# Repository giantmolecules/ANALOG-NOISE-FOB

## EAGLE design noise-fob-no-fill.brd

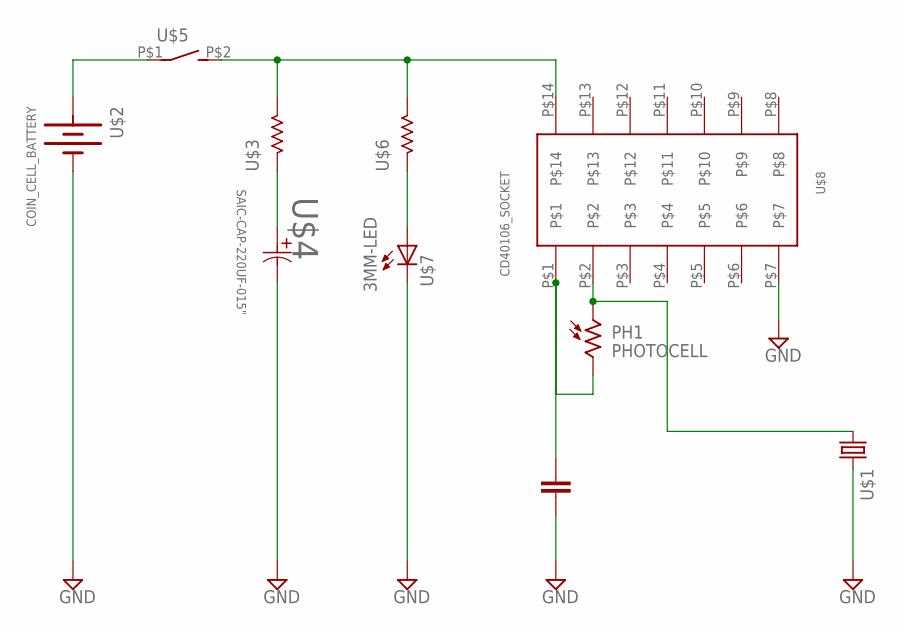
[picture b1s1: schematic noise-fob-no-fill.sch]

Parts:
PH1: PHOTOCELL
U$1: PIEZO_BUZZER_2
U$2: COIN_CELL_BATTERY; COIN_BATTERY
U$3, U$6: RESISTOR-1/4W-THROUGH-HOLE; 1/4W_TH_RESISTOR
U$4: SAIC-CAP-220UF-015"; SAIC-CAP-0.15"-LEAD-SPACING-01
U$5: TACTILE_SWITCH
U$7: 3MM-LED; LED3MM
U$8: CD40106_SOCKET; DIP_14_SOCKET
U$10: SAIC-CAP-0.1UF-02"; SAIC-CAP-0.2"-LEAD-SPACING-03

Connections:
GND: U$1.P$2 (2), U$2.P$2 (-), U$4.P$2 (22), U$7.K (2), U$8.P$7, U$10.P$1 (1)
unnamed: U$2.P$1 (+), U$5.P$1
unnamed: U$3.P$2, U$5.P$2 (S), U$6.P$2, U$8.P$14
unnamed: U$3.P$1, U$4.P$1 (11)
unnamed: U$6.P$1, U$7.A (1)
unnamed: PH1.P$1 (1), U$1.P$1 (1), U$8.P$2
unnamed: PH1.P$2 (2), U$8.P$1, U$10.P$2 (2)

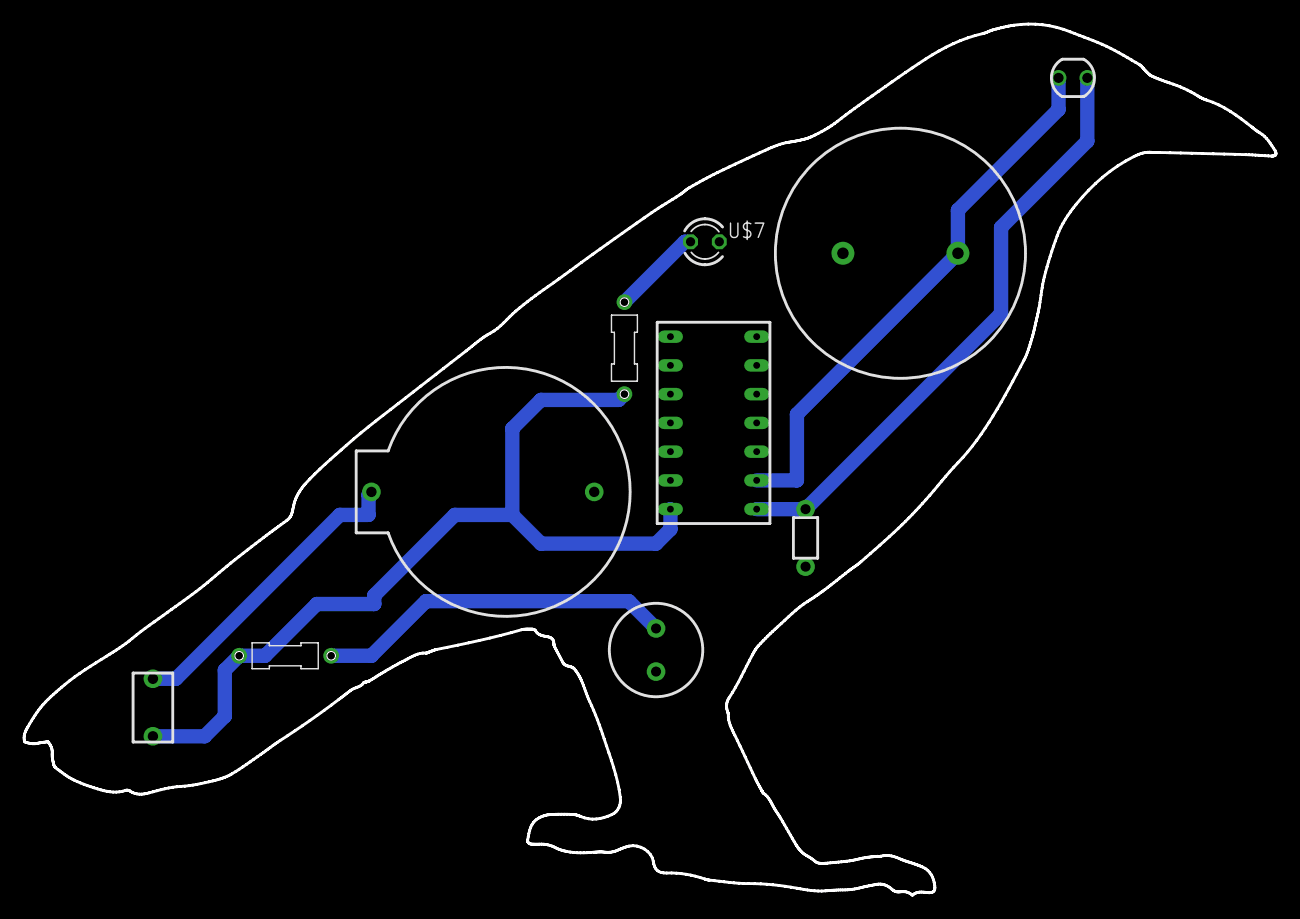
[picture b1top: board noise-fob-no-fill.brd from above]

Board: 2 copper layers, 110.6 x 77.0 mm, 10 parts (0 on the bottom side), 7 nets.

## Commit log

2020-03-03 init
2020-03-03 finished
